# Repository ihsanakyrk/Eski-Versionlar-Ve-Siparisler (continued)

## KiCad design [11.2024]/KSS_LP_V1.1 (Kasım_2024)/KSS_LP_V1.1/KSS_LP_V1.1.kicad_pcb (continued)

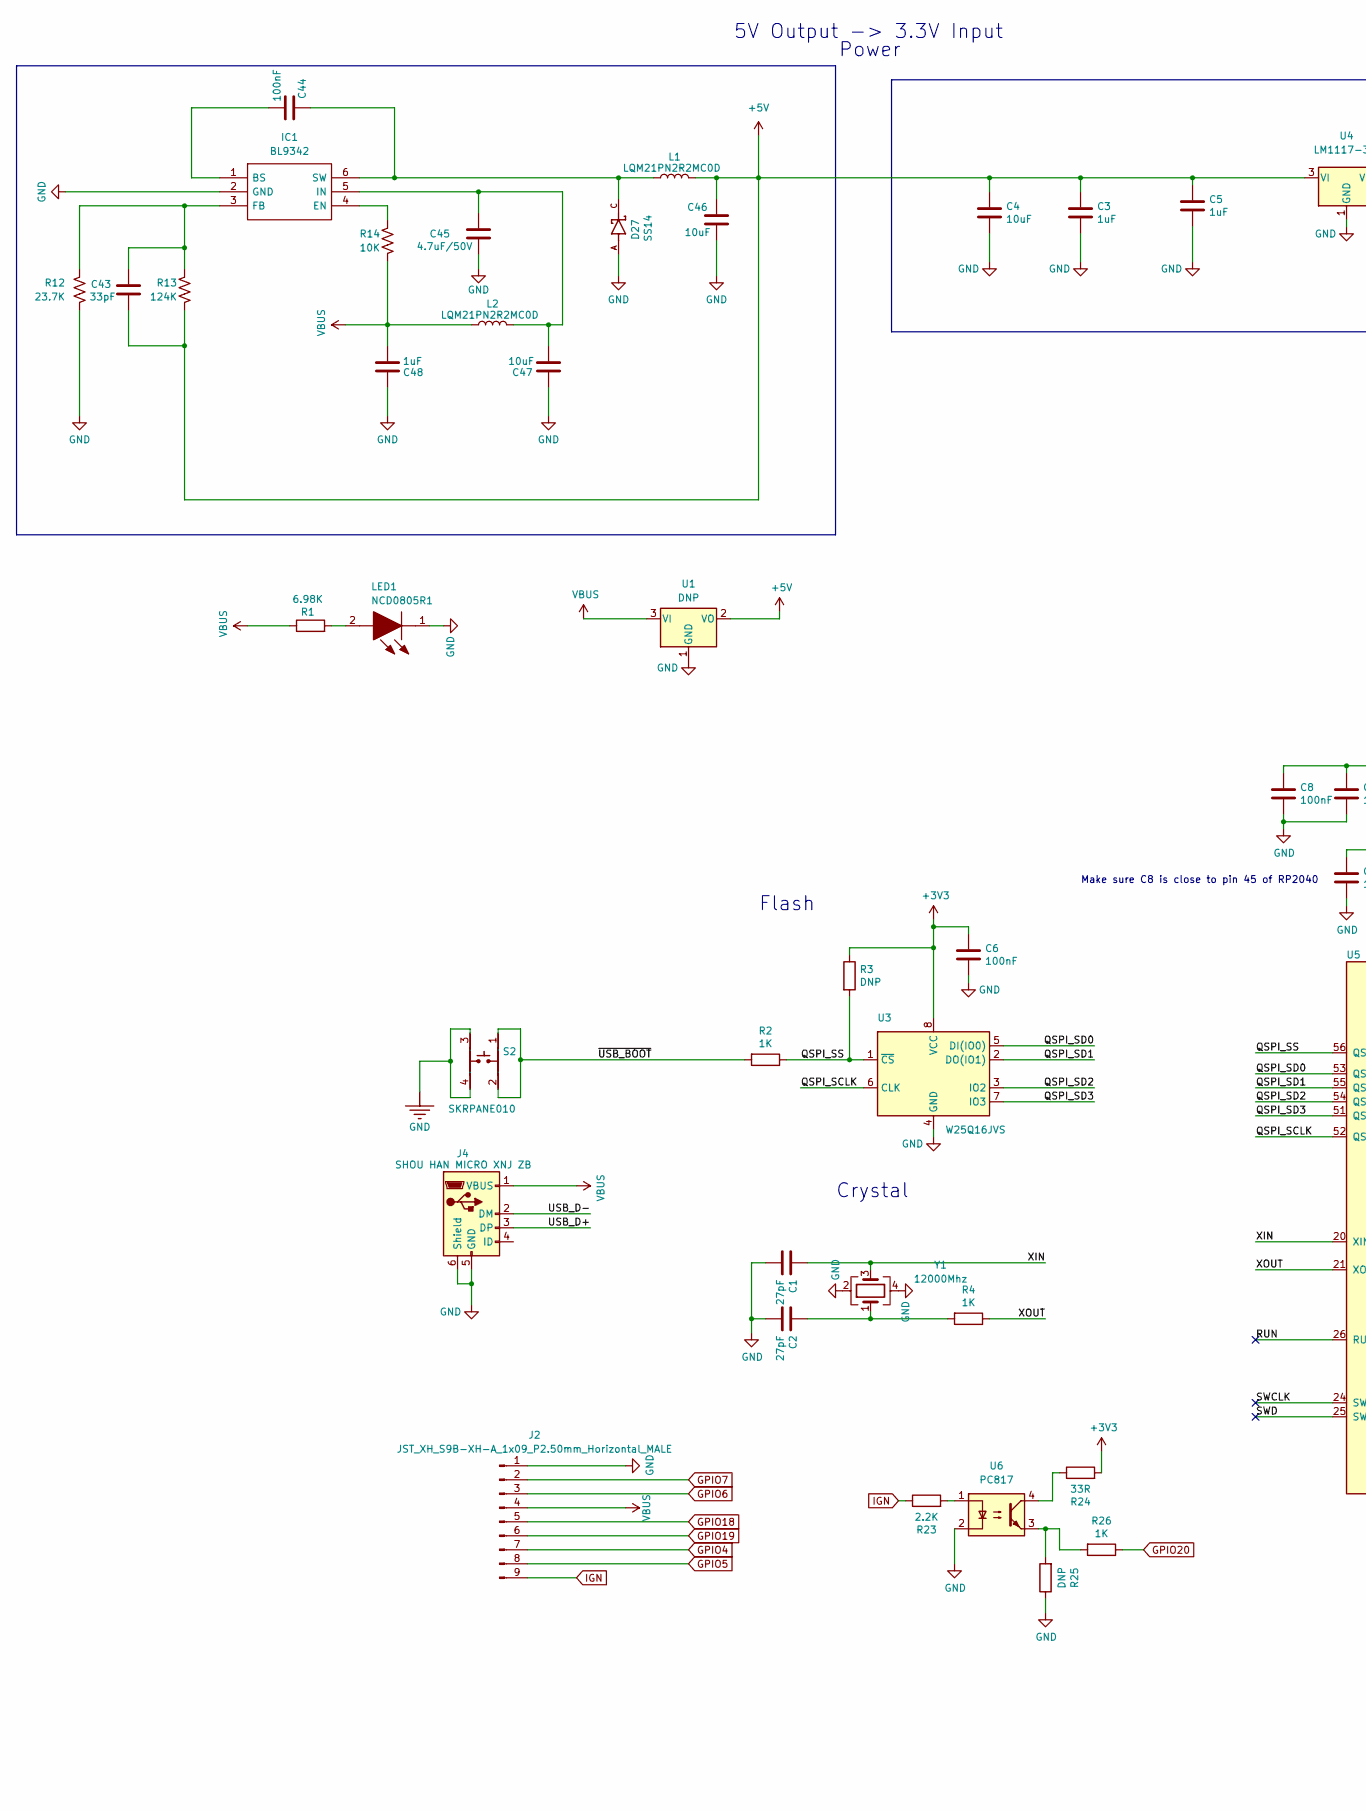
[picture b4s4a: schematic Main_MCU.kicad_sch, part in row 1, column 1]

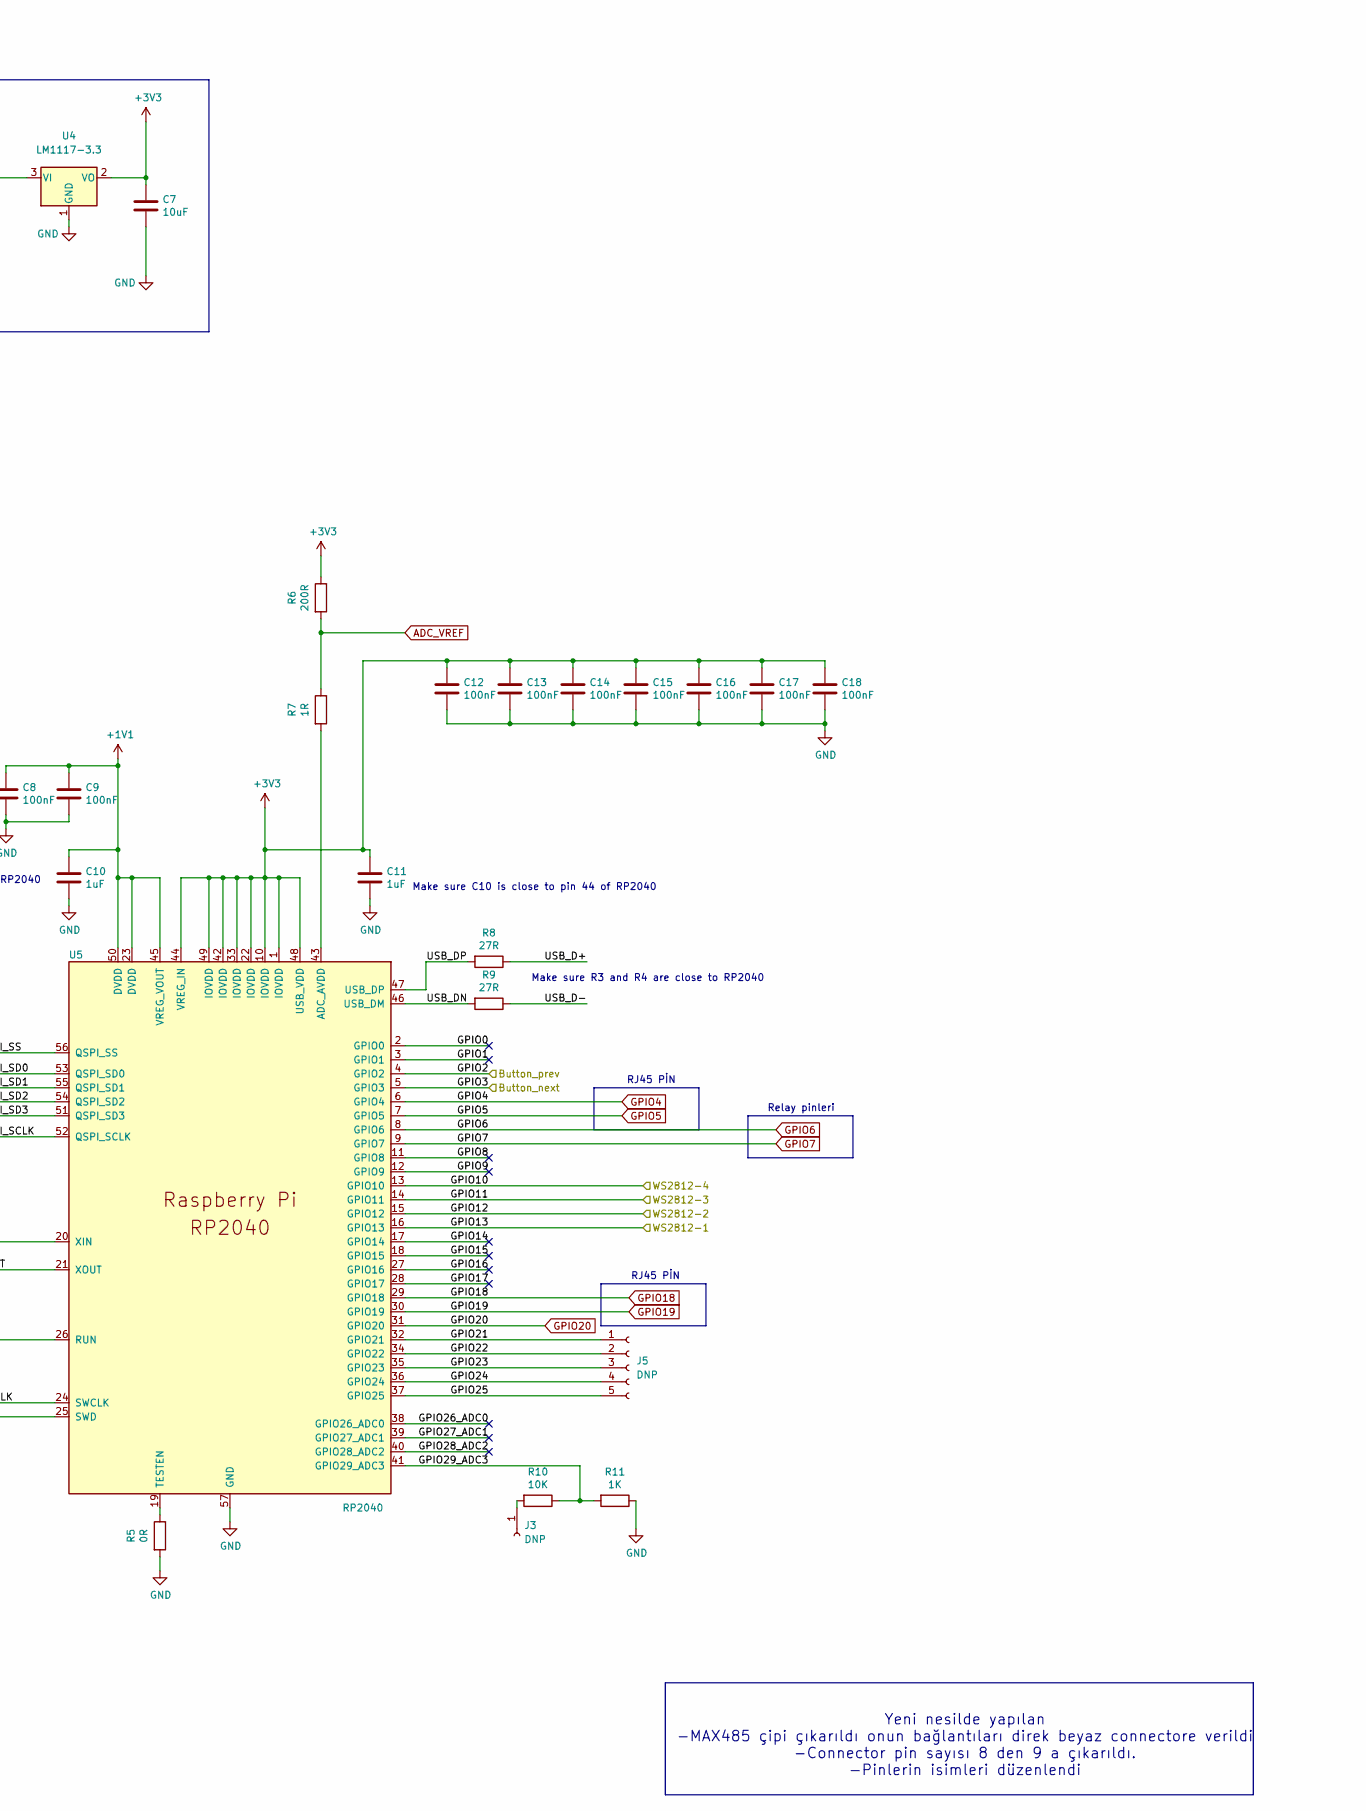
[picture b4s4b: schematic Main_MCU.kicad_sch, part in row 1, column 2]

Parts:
C1, C2: 27pF; C_0402_1005Metric
C3, C5: 1uF; C_0805_2012Metric
C4, C7: 10uF; C_0805_2012Metric
C6, C8, C9, C12, C13, C14, C15, C16, C17, C18: 100nF; C_0402_1005Metric
C10, C11: 1uF; C_0402_1005Metric
C43: 33pF; C_0603_1608Metric; MPN CL10C330JB8NNNC
C44: 100nF; C_0603_1608Metric; MPN 0603B104K500NT
C45: 4.7uF/50V; C_0603_1608Metric
C46, C47: 10uF; C_0603_1608Metric; MPN CL10A106MO8NQNC
C48: 1uF; C_0603_1608Metric
D27: SS14; MPN SS14 SOD-123FL
IC1: BL9342; SOT-23-6; MPN BL9342
J2: JST_XH_S9B-XH-A_1x09_P2.50mm_Horizontal_MALE; JST_XH_S9B-XH-A_1x09_P2.50mm_Horizontal
J3: DNP; PinHeader_1x01_P1.00mm_Vertical
J4: SHOU HAN MICRO XNJ ZB; Micro-B SMD; MPN SHOU HAN MICRO XNJ ZB
J5: DNP; PinHeader_1x05_P2.00mm_Vertical
L1, L2: LQM21PN2R2MC0D; L_0805_2012Metric; MPN LQM21PN2R2MC0D
LED1: NCD0805R1; LED_0805_2012Metric; Manufacturer_Part_Number 150080VS75000; Mouser Part Number 710-150080VS75000
R1: 6.98K; C_0402_1005Metric
R2, R4, R11, R26: 1K; C_0402_1005Metric
R3, R25: DNP; C_0402_1005Metric
R5: 0R; C_0402_1005Metric
R6: 200R; C_0402_1005Metric
R7: 1R; C_0402_1005Metric
R8, R9: 27R; C_0402_1005Metric
R10: 10K; C_0402_1005Metric
R12: 23.7K; R_0603_1608Metric
R13: 124K; R_0603_1608Metric
R14: 10K; R_0603_1608Metric; MPN 0603WAF1002T5E
R23: 2.2K; C_0402_1005Metric
R24: 33R; C_0402_1005Metric
S2: SKRPANE010
U1: DNP; SOT-223-3_TabPin2
U3: W25Q16JVS; SOIC-8_5.23x5.23mm_P1.27mm
U4: LM1117-3.3; SOT-223-3_TabPin2
U5: RP2040; RP2040-QFN-56
U6: PC817; DIP-4_W7.62mm_SMDSocket_SmallPads
Y1: 12000Mhz; Crystal_SMD_3225-4Pin_3.2x2.5mm

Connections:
+1V1: C8.1, C9.1, C10.1, U5.23 (DVDD), U5.45 (VREG_VOUT), U5.50 (DVDD)
+3V3: C6.1, C7.1, C11.1, C12.1, C13.1, C14.1, C15.1, C16.1, C17.1, C18.1, R3.1, R6.1, R24.2, U3.8 (VCC), U4.2 (VO), U5.1 (IOVDD), U5.10 (IOVDD), U5.22 (IOVDD), U5.33 (IOVDD), U5.42 (IOVDD), U5.44 (VREG_IN), U5.48 (USB_VDD), U5.49 (IOVDD)
+5V: C3.1, C4.1, C5.1, C43.1, C46.2, L1.1, R13.2, U1.2 (VO), U4.3 (VI); also elsewhere on the board
/Main_MCU/GPIO0: U5.2 (GPIO0)
/Main_MCU/GPIO1: U5.3 (GPIO1)
/Main_MCU/GPIO2: U5.4 (GPIO2); also elsewhere on the board
/Main_MCU/GPIO3: U5.5 (GPIO3); also elsewhere on the board
/Main_MCU/GPIO8: U5.11 (GPIO8)
/Main_MCU/GPIO9: U5.12 (GPIO9)
/Main_MCU/GPIO10: U5.13 (GPIO10); also elsewhere on the board
/Main_MCU/GPIO11: U5.14 (GPIO11); also elsewhere on the board
/Main_MCU/GPIO12: U5.15 (GPIO12); also elsewhere on the board
/Main_MCU/GPIO13: U5.16 (GPIO13); also elsewhere on the board
/Main_MCU/GPIO14: U5.17 (GPIO14)
/Main_MCU/GPIO15: U5.18 (GPIO15)
/Main_MCU/GPIO16: U5.27 (GPIO16)
/Main_MCU/GPIO17: U5.28 (GPIO17)
/Main_MCU/GPIO21: J5.1, U5.32 (GPIO21)
/Main_MCU/GPIO22: J5.2, U5.34 (GPIO22)
/Main_MCU/GPIO23: J5.3, U5.35 (GPIO23)
/Main_MCU/GPIO24: J5.4, U5.36 (GPIO24)
/Main_MCU/GPIO25: J5.5, U5.37 (GPIO25)
/Main_MCU/GPIO26_ADC0: U5.38 (GPIO26_ADC0)
/Main_MCU/GPIO27_ADC1: U5.39 (GPIO27_ADC1)
/Main_MCU/GPIO28_ADC2: U5.40 (GPIO28_ADC2)
/Main_MCU/GPIO29_ADC3: R10.1, R11.2, U5.41 (GPIO29_ADC3)
/Main_MCU/QSPI_SCLK: U3.6 (CLK), U5.52 (QSPI_SCLK)
/Main_MCU/QSPI_SD0: U3.5 (DI(IO0)), U5.53 (QSPI_SD0)
/Main_MCU/QSPI_SD1: U3.2 (DO(IO1)), U5.55 (QSPI_SD1)
/Main_MCU/QSPI_SD2: U3.3 (IO2), U5.54 (QSPI_SD2)
/Main_MCU/QSPI_SD3: U3.7 (IO3), U5.51 (QSPI_SD3)
/Main_MCU/QSPI_SS: R2.1, R3.2, U3.1 (~CS), U5.56 (QSPI_SS)
/Main_MCU/RUN: U5.26 (RUN)
/Main_MCU/SWCLK: U5.24 (SWCLK)
/Main_MCU/SWD: U5.25 (SWD)
/Main_MCU/USB_D+: J4.3 (DP), R8.1
/Main_MCU/USB_D-: J4.2 (DM), R9.1
/Main_MCU/USB_DN: R9.2, U5.46 (USB_DM)
/Main_MCU/USB_DP: R8.2, U5.47 (USB_DP)
/Main_MCU/XIN: C1.1, U5.20 (XIN), Y1.3
/Main_MCU/XOUT: R4.1, U5.21 (XOUT)
/Main_MCU/~USB_BOOT: R2.2, S2.1, S2.2
ADC_VREF: R6.2, R7.1
GND: C1.2, C2.2, C3.2, C4.2, C5.2, C6.2, C7.2, C8.2, C9.2, C10.2, C11.2, C12.2, C13.2, C14.2, C15.2, C16.2, C17.2, C18.2, C45.1, C46.1, C47.1, C48.1, D27.A, IC1.2 (GND), J2.1, J4.5 (GND), J4.6 (Shield), LED1.1, R5.2, R11.1, R12.2, R25.1, S2.3, S2.4, U1.1 (GND), U3.4 (GND), U4.1 (GND), U5.57 (GND), U6.2, Y1.2, Y1.4; also elsewhere on the board
GPIO4: J2.7, U5.6 (GPIO4)
GPIO5: J2.8, U5.7 (GPIO5)
GPIO6: J2.3, U5.8 (GPIO6)
GPIO7: J2.2, U5.9 (GPIO7)
GPIO18: J2.5, U5.29 (GPIO18)
GPIO19: J2.6, U5.30 (GPIO19)
GPIO20: R26.1, U5.31 (GPIO20)
IGN: J2.9, R23.1
unnamed: C2.1, R4.2, Y1.1
unnamed: C44.1, IC1.1 (BS)
unnamed: IC1.4 (EN), R14.1
unnamed: C43.2, IC1.3 (FB), R12.1, R13.1
unnamed: C45.2, C47.2, IC1.5 (IN), L2.1
unnamed: C44.2, D27.C, IC1.6 (SW), L1.2
unnamed: J3.1, R10.2
unnamed: LED1.2, R1.2
unnamed: R23.2, U6.1
unnamed: R24.1, U6.4
unnamed: R25.2, R26.2, U6.3
unnamed: R7.2, U5.43 (ADC_AVDD)
unnamed: R5.1, U5.19 (TESTEN)
VBUS: C48.2, J2.4, J4.1 (VBUS), L2.2, R1.1, R14.2, U1.3 (VI)

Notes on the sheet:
RJ45 PİN
Flash
Make sure C10 is close to pin 44 of RP2040
Relay pinleri
Power
Make sure C8 is close to pin 45 of RP2040
Crystal
5V Output -> 3.3V Input
Make sure R3 and R4 are close to RP2040
Yeni nesilde yapılan -MAX485 çipi çıkarıldı onun bağlantıları direk beyaz connectore verildi -Connector pin sayısı 8 den 9 a çıkarıldı. -Pinlerin isimleri düzenlendi

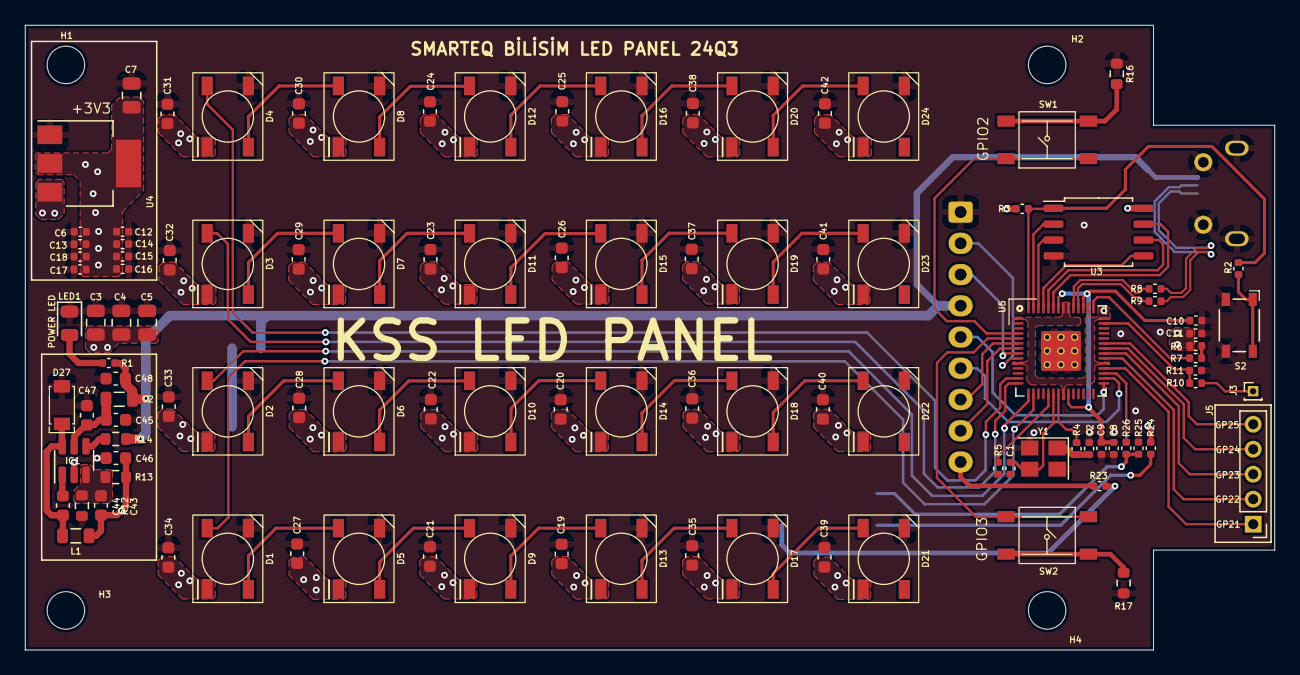
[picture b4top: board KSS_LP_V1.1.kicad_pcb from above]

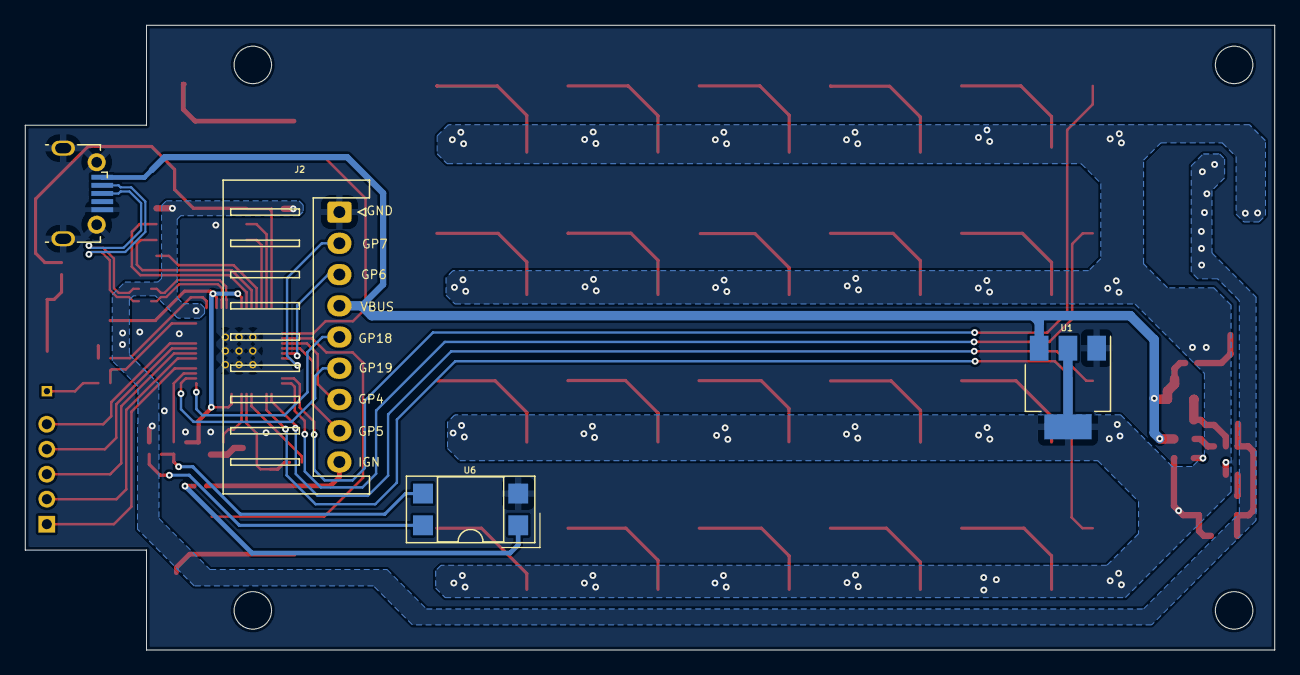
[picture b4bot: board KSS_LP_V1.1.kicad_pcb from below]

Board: 2 copper layers, 100.0 x 50.0 mm, 114 parts (4 on the bottom side), 74 nets.

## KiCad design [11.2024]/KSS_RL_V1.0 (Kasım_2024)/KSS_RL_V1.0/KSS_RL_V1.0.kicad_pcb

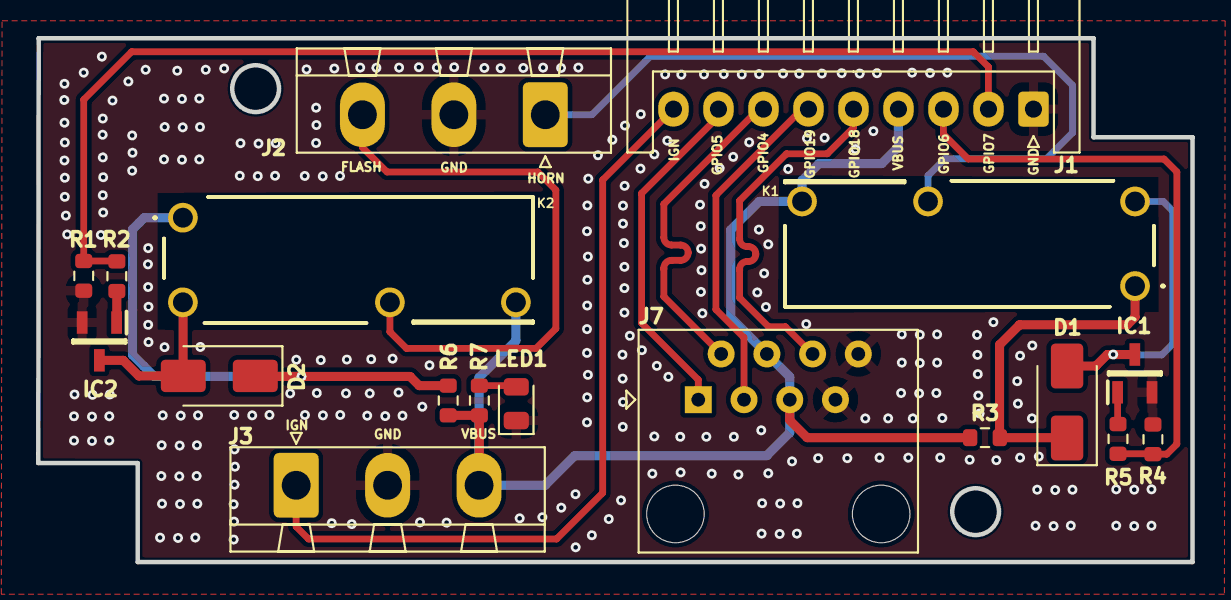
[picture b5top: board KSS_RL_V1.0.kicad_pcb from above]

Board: 2 copper layers, 64.1 x 29.1 mm, 18 parts (0 on the bottom side), 18 nets.

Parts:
D1, D2: MRA4007T3G; D_SMA
IC1, IC2: MMBT2222ALT1G; SOT96P237X111-3N
J1: JST_XH_S9B-XH-A_1x09_P2.50mm_Horizontal_MALE; JST_XH_S9B-XH-A_1x09_P2.50mm_Horizontal
J2, J3: DNP; KF2EDGR-Y-5.08-03P-1 B
J7: 8P8C; RJ45_Amphenol_54602-x08_Horizontal
K1, K2: HF46F5HS1
LED1: NCD0805R1; LED_0805_2012Metric
R1, R2, R4, R5: 10K; R_0603_1608Metric
R3, R6: 0R; R_0603_1608Metric
R7: 3.3K; R_0603_1608Metric

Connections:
/Flash: J2.3, K2.3
/HORN: J2.1, K1.3
GND: IC1.2 (E), IC2.2 (E), J1.1, J2.2, J3.2, J7.7, J7.8, LED1.1, R1.1, R4.1
GPIO4: J1.7, J7.2
GPIO5: J1.8, J7.1
GPIO6: J1.3, R4.2, R5.2
GPIO7: J1.2, R1.2, R2.2
GPIO18: J1.5, J7.6
GPIO19: J1.6, J7.3
IGN: J1.9, J3.1
unnamed: D1.2 (A), IC1.3 (C), K1.2
unnamed: D1.1 (K), K1.1, R3.1
unnamed: D2.2 (A), IC2.3 (C), K2.2
unnamed: D2.1 (K), K2.1, R6.1
unnamed: IC1.1 (B), R5.1
unnamed: IC2.1 (B), R2.1
unnamed: LED1.2, R7.2
VBUS: J1.4, J3.3, J7.4, J7.5, K1.4, K2.4, R3.2, R6.2, R7.1
